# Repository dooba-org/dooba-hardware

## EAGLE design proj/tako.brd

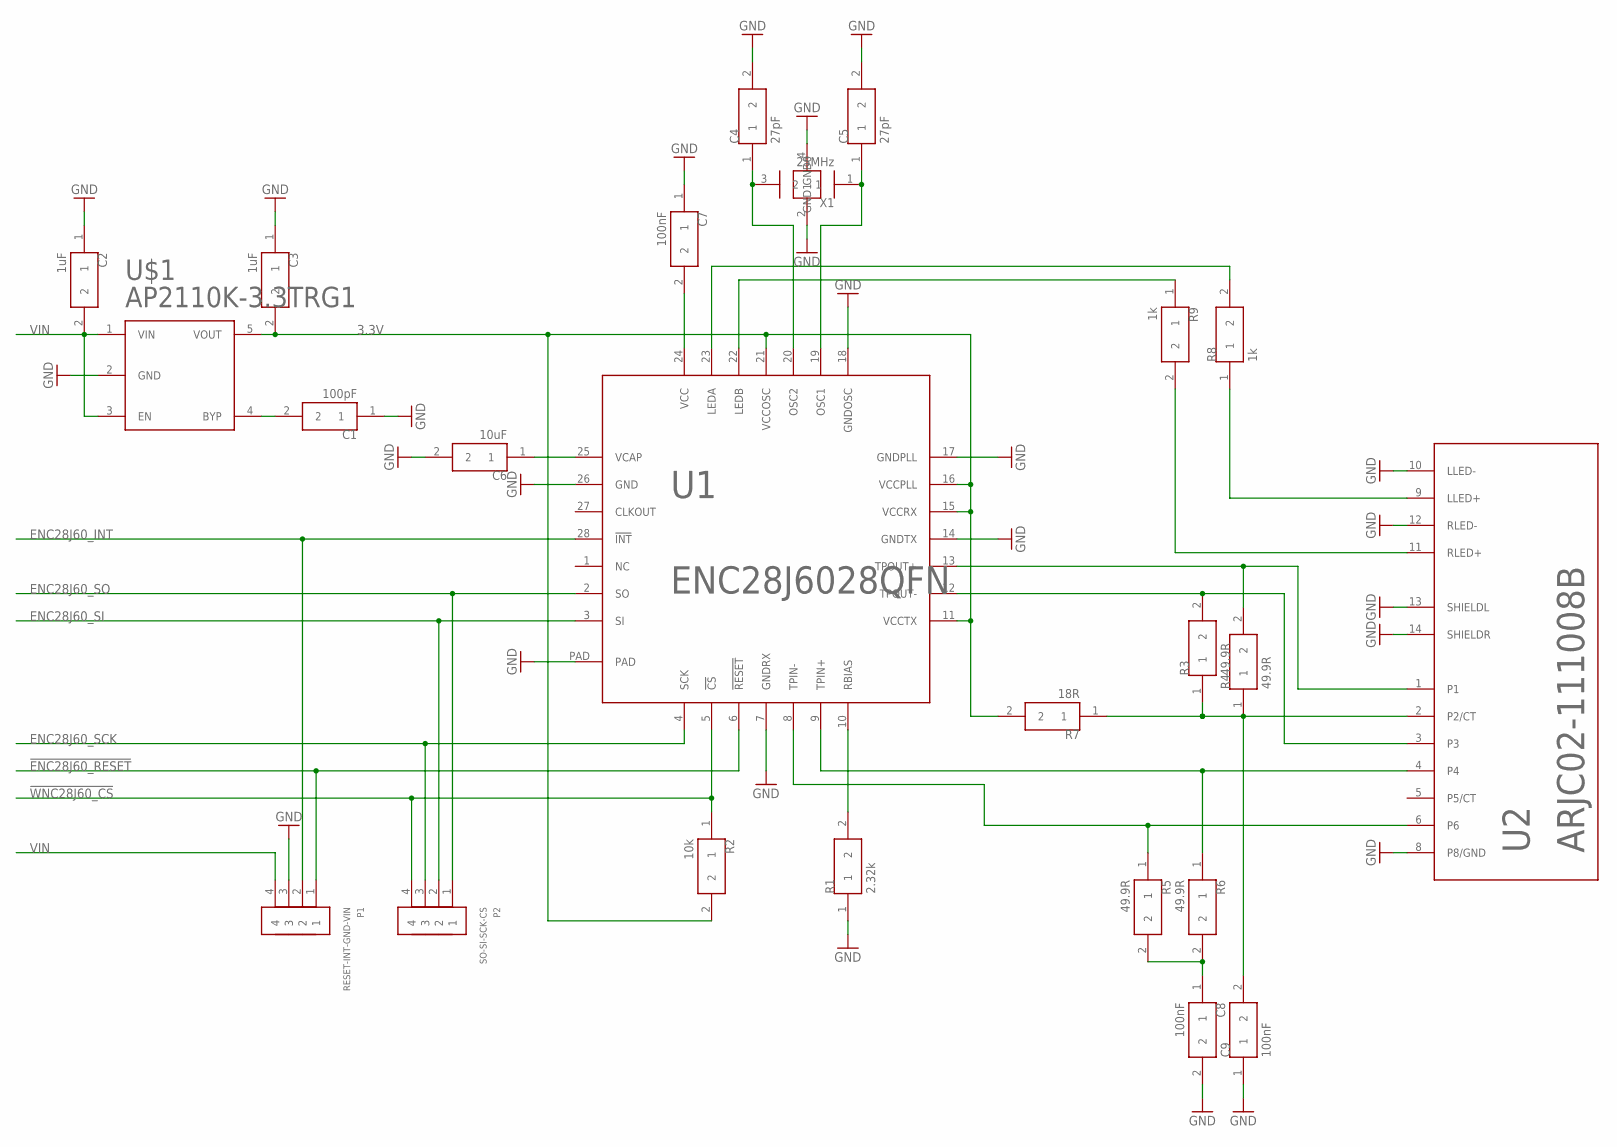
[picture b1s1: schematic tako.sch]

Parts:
C1: 100pF; 0805
C2, C3: 1uF; 0805
C4, C5: 27pF; 0805
C6: 10uF; 0805
C7, C8, C9: 100nF; 0805
P1: RESET-INT-GND-VIN; PIN_4
P2: SO-SI-SCK-CS; PIN_4
R1: 2.32k; 0805
R2: 10k; 0805
R3, R4, R5, R6: 49.9R; 0805
R7: 18R; 0805
R8, R9: 1k; 0805
U1: ENC28J6028QFN; 28-QFN
U2: ARJC02-111008B
U$1: AP2110K-3.3TRG1; SOT23-5
X1: 25MHz; XTAL_3225

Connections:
3.3V: C3.2, R2.2, R7.2, U1.11 (VCCTX), U1.15 (VCCRX), U1.16 (VCCPLL), U1.21 (VCCOSC), U$1.5 (VOUT)
!ENC28J60_RESET: P1.1, U1.6 (!RESET)
!WNC28J60_CS: P2.4, R2.1, U1.5 (!CS)
ENC28J60_INT: P1.2, U1.28 (!INT)
ENC28J60_SCK: P2.3, U1.4 (SCK)
ENC28J60_SI: P2.2, U1.3 (SI)
ENC28J60_SO: P2.1, U1.2 (SO)
GND: C1.1, C2.1, C3.1, C4.2, C5.2, C6.2, C7.1, C8.2, C9.1, P1.3, R1.1, U1.7 (GNDRX), U1.14 (GNDTX), U1.17 (GNDPLL), U1.18 (GNDOSC), U1.26 (GND), U1.PAD, U2.8 (P8/GND), U2.10 (LLED-), U2.12 (RLED-), U2.13 (SHIELDL), U2.14 (SHIELDR), U$1.2 (GND), X1.2 (GND0), X1.4 (GND1)
unnamed: C4.1, U1.20 (OSC2), X1.3 (2)
unnamed: C5.1, U1.19 (OSC1), X1.1
unnamed: C1.2, U$1.4 (BYP)
unnamed: C6.1, U1.25 (VCAP)
unnamed: C7.2, U1.24 (VCC)
unnamed: R1.2, U1.10 (RBIAS)
unnamed: R6.1, U1.9 (TPIN+), U2.4
unnamed: R5.1, U1.8 (TPIN-), U2.6
unnamed: R3.2, U1.12 (TPOUT-), U2.3
unnamed: R4.2, U1.13 (TPOUT+), U2.1
unnamed: C8.1, R5.2, R6.2
unnamed: R9.1, U1.22 (LEDB)
unnamed: R8.2, U1.23 (LEDA)
unnamed: R8.1, U2.9 (LLED+)
unnamed: C9.2, R3.1, R4.1, R7.1, U2.2 (P2/CT)
unnamed: R9.2, U2.11 (RLED+)
VIN: C2.2, P1.4, U$1.1 (VIN), U$1.3 (EN)

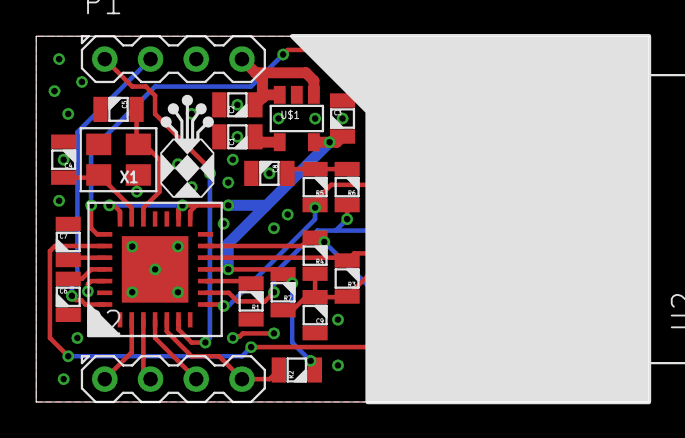
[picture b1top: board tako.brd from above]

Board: 2 copper layers, 34.0 x 20.3 mm, 24 parts (0 on the bottom side), 25 nets.
